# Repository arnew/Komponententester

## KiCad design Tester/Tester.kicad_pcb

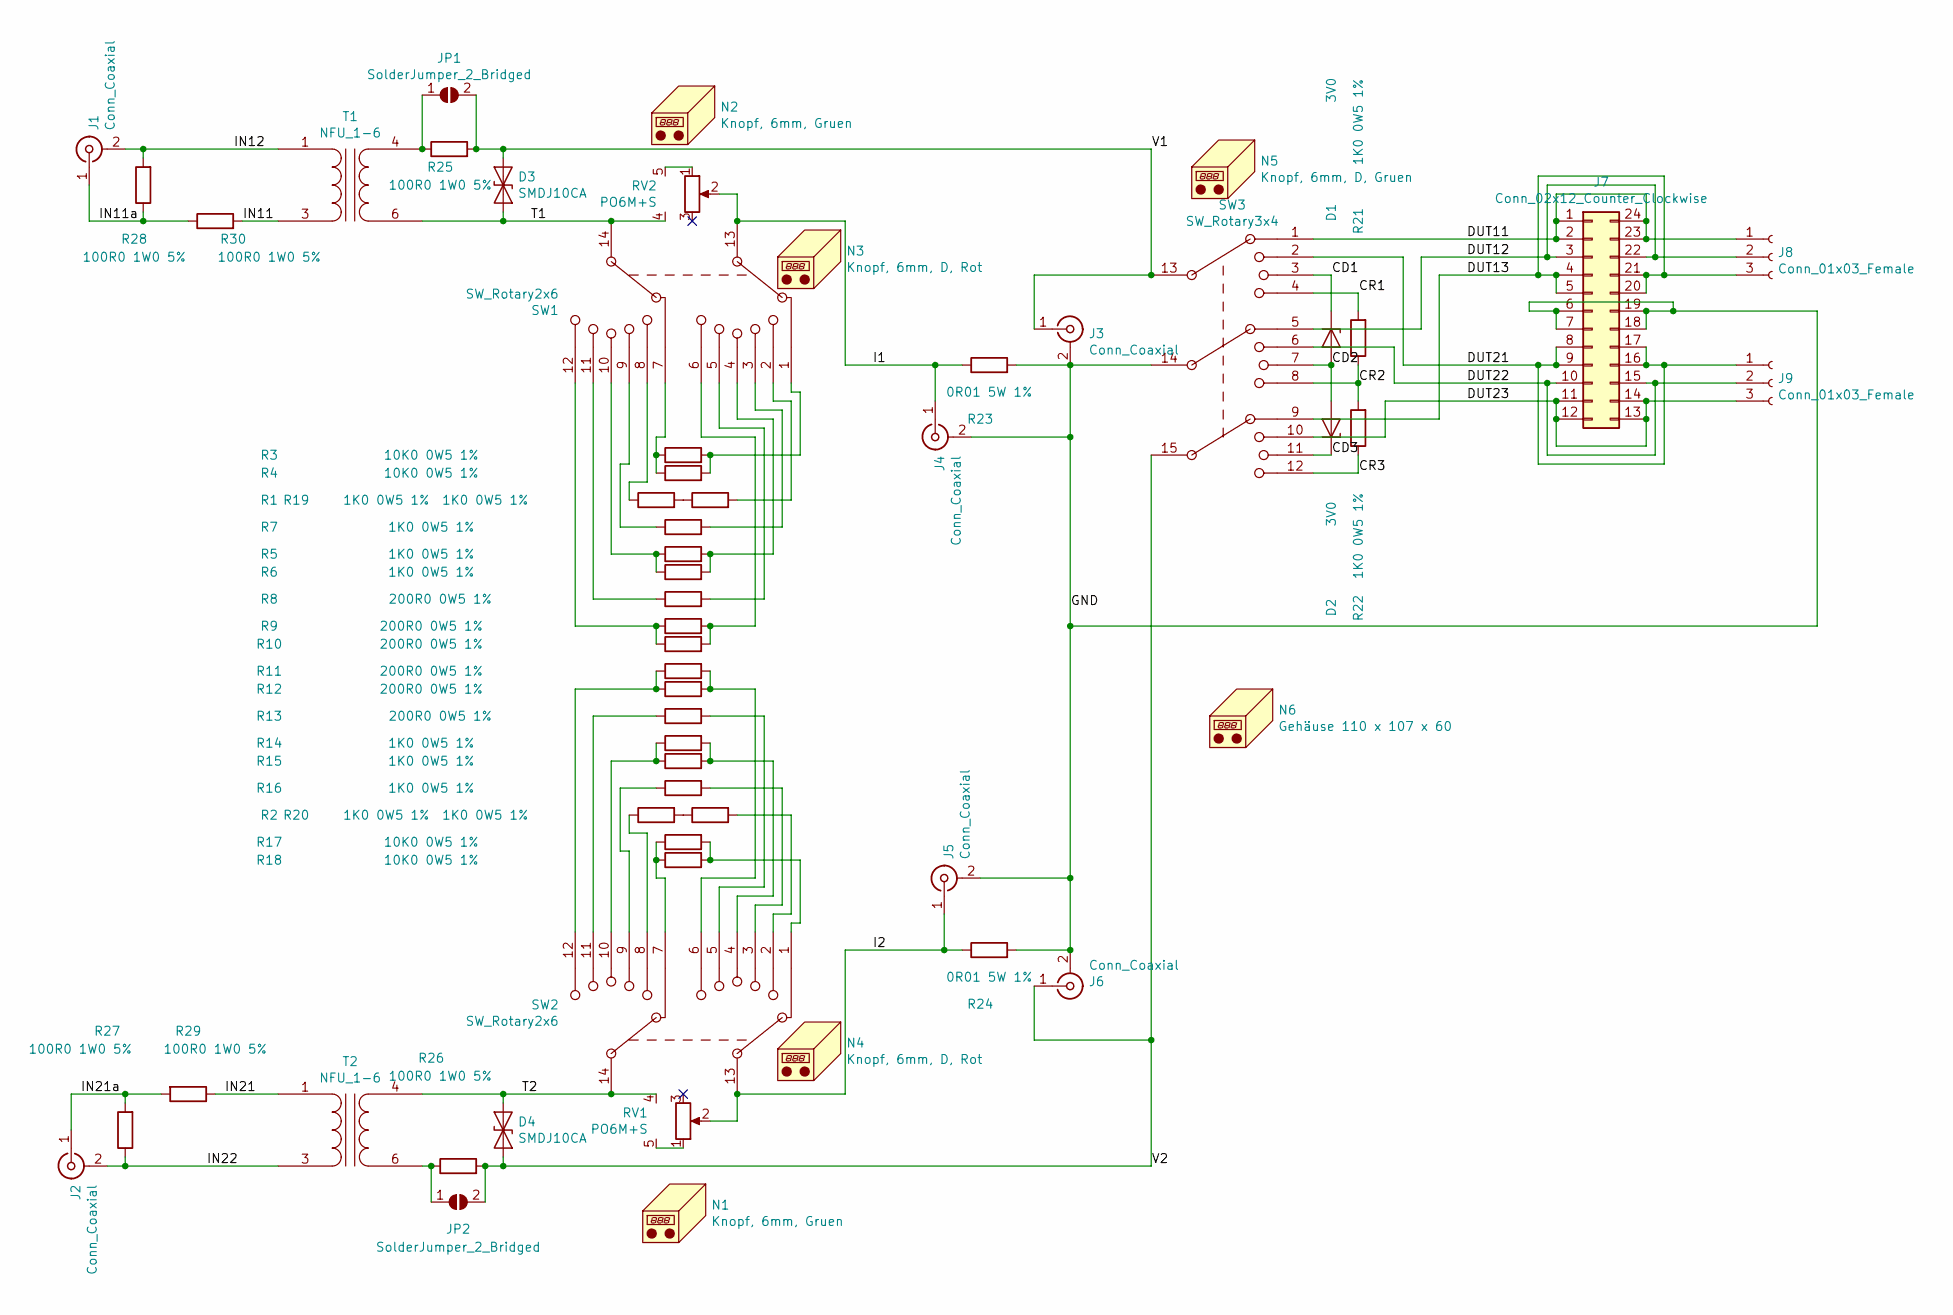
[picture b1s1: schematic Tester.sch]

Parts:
D1, D2: 3V0; SOT-23_Handsoldering
D3, D4: SMDJ10CA; D_SMB-SMC_Universal_Handsoldering
J1, J2, J3, J4, J5, J6: Conn_Coaxial; BNC_Amphenol_B6252HB-NPP3G-50_Horizontal
J7: Conn_02x12_Counter_Clockwise; DIP_Socket-24_W11.9_W12.7_W15.24_W17.78_W18.5_3M_224-1275-0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
J8, J9: Conn_01x03_Female; TerminalBlock_WAGO_236-403_1x03_P5.00mm_45Degree
JP1, JP2: SolderJumper_2_Bridged; SolderJumper-2_P1.3mm_Open_TrianglePad1.0x1.5mm
N1, N2: Knopf, 6mm, Gruen; BOM_ONLY
N3, N4: Knopf, 6mm, D, Rot; BOM_ONLY
N5: Knopf, 6mm, D, Gruen; BOM_ONLY
N6: Gehäuse 110 x 107 x 60; BOM_ONLY
R1, R2, R5, R6, R7, R14, R15, R16, R19, R20, R21, R22: 1K0 0W5 1%; R_1206_3216Metric_Pad1.42x1.75mm_HandSolder
R3, R4, R17, R18: 10K0 0W5 1%; R_1206_3216Metric_Pad1.42x1.75mm_HandSolder
R8, R9, R10, R11, R12, R13: 200R0 0W5 1%; R_1206_3216Metric_Pad1.42x1.75mm_HandSolder
R23, R24: 0R01 5W 1%; R_2512_6332Metric_Pad1.52x3.35mm_HandSolder
R25, R26, R27, R28, R29, R30: 100R0 1W0 5%; R_2512_6332Metric_Pad1.52x3.35mm_HandSolder
RV1, RV2: PO6M+S
SW1, SW2: SW_Rotary2x6; RND210-00068
SW3: SW_Rotary3x4; RND210-00076
T1, T2: NFU_1-6; NFU_1-1

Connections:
/CD1: D1.3 (K), SW3.3
/CD2: D1.1 (A), D2.1 (A), SW3.7
/CD3: D2.3 (K), SW3.11
/CR1: R21.2, SW3.4
/CR2: R21.1, R22.2, SW3.8
/CR3: R22.1, SW3.12
/DUT11: J7.1, J7.2, J7.23, J7.24, J8.1, SW3.1
/DUT12: J7.3, J7.22, J8.2, SW3.5
/DUT13: J7.4, J7.5, J7.20, J7.21, J8.3, SW3.9
/DUT21: J7.8, J7.9, J7.16, J7.17, J9.1, SW3.2
/DUT22: J7.10, J7.15, J9.2, SW3.6
/DUT23: J7.11, J7.12, J7.13, J7.14, J9.3, SW3.10
/GND: J3.2 (Ext), J4.2 (Ext), J5.2 (Ext), J6.2 (Ext), J7.6, J7.7, J7.18, J7.19, R23.2, R24.2, SW3.14
/I1: J4.1 (In), R23.1, RV2.2, SW1.13
/I2: J5.1 (In), R24.1, RV1.2, SW2.13
/IN11: R30.2, T1.3 (AB)
/IN11a: J1.1 (In), R28.1, R30.1
/IN12: J1.2 (Ext), R28.2, T1.1 (AA)
/IN21: R29.1, T2.1 (AA)
/IN21a: J2.1 (In), R27.2, R29.2
/IN22: J2.2 (Ext), R27.1, T2.3 (AB)
/T1: D3.2 (A2), RV2.4, SW1.14, T1.6 (SA)
/T2: D4.1 (A1), RV1.4, SW2.14, T2.4 (SB)
/V1: D3.1 (A1), J3.1 (In), JP1.2 (B), R25.2, SW3.13
/V2: D4.2 (A2), J6.1 (In), JP2.2 (B), R26.2, SW3.15
unnamed: JP1.1 (A), R25.1, T1.4 (SB)
unnamed: JP2.1 (A), R26.1, T2.6 (SA)
unnamed: R1.1, SW1.8
unnamed: R1.2, R19.1
unnamed: R2.1, SW2.8
unnamed: R2.2, R20.1
unnamed: R3.1, R4.1, SW1.7
unnamed: R3.2, R4.2, SW1.1
unnamed: R5.1, R6.1, SW1.10
unnamed: R5.2, R6.2, SW1.4
unnamed: R7.1, SW1.9
unnamed: R7.2, SW1.3
unnamed: R8.1, SW1.11
unnamed: R8.2, SW1.5
unnamed: R9.1, R10.1, SW1.12
unnamed: R9.2, R10.2, SW1.6
unnamed: R11.1, R12.1, SW2.12
unnamed: R11.2, R12.2, SW2.6
unnamed: R13.1, SW2.11
unnamed: R13.2, SW2.5
unnamed: R14.1, R15.1, SW2.10
unnamed: R14.2, R15.2, SW2.4
unnamed: R16.1, SW2.9
unnamed: R16.2, SW2.3
unnamed: R17.1, R18.1, SW2.7
unnamed: R17.2, R18.2, SW2.1
unnamed: R19.2, SW1.2
unnamed: R20.2, SW2.2
unnamed: RV1.1, RV1.5
unnamed: RV2.1, RV2.5

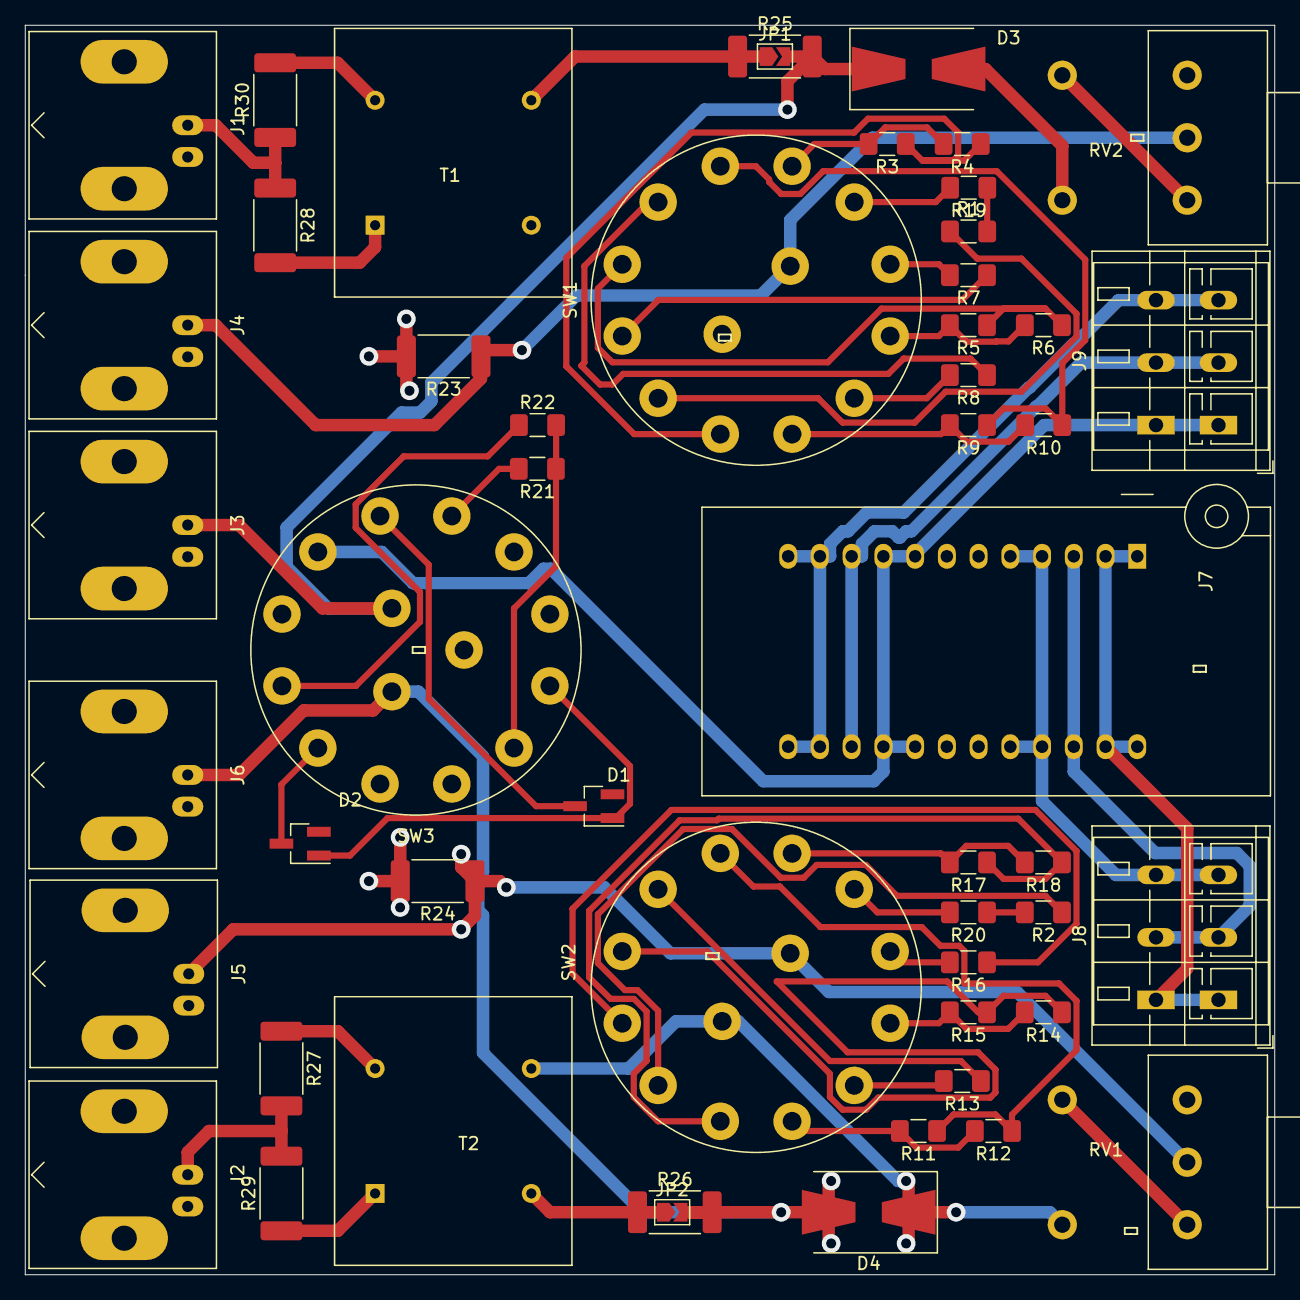
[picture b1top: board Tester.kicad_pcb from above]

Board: 4 copper layers, 100.0 x 100.0 mm, 58 parts (0 on the bottom side), 55 nets.

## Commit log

2020-06-21 add everything
2020-06-21 routing
